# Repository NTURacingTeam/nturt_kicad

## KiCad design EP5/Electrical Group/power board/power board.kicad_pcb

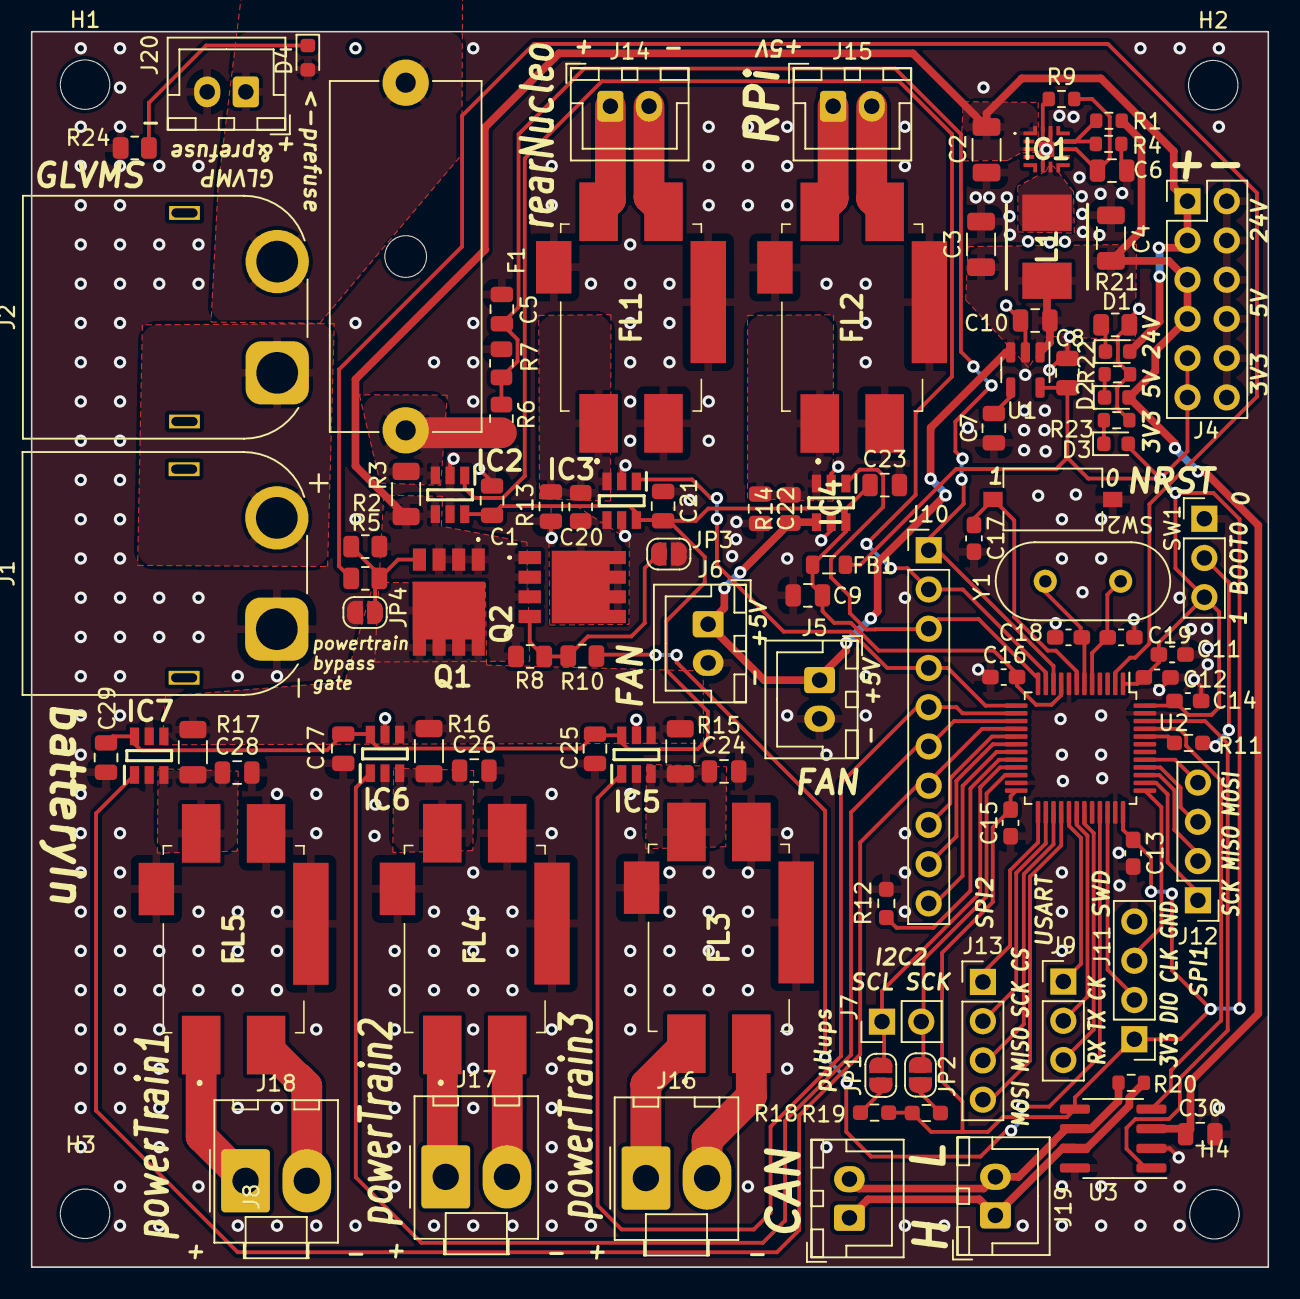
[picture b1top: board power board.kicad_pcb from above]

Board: 2 copper layers, 80.0 x 80.0 mm, 108 parts (0 on the bottom side), 76 nets.

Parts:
C1, C21, C25: 0u1 10V; C_0805_2012Metric
C2: 10u 35V; C_1206_3216Metric
C3, C4: 22u 16V; C_1206_3216Metric
C5: 1u 10V; C_0805_2012Metric
C6: 1u 16V; C_0805_2012Metric
C7: 10nF; C_0805_2012Metric
C8, C9: 10u 5V; C_0805_2012Metric
C10: 4u7 10V; C_0805_2012Metric
C11, C16: 10u; C_0603_1608Metric_Pad1.08x0.95mm_HandSolder
C12, C13, C14, C15, C17: 100n; C_0603_1608Metric_Pad1.08x0.95mm_HandSolder
C18, C19: 30p; C_0603_1608Metric_Pad1.08x0.95mm_HandSolder
C20, C22, C24, C26, C28: 10n; C_0805_2012Metric
C23, C27, C29: 0u1; C_0805_2012Metric
C30: 0u1 16V; C_0805_2012Metric
D1, D4: 24VGood; LED_0603_1608Metric
D2: 5VGood; LED_0603_1608Metric
D3: 3V3Good; LED_0603_1608Metric
F1: Fuse; Fuseholder_Cylinder-5x20mm_Schurter_0031_8201_Horizontal_Op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
FB1: FerriteBead; L_0805_2012Metric
FL1, FL2, FL3, FL4, FL5: BNX026H01L; BNX024H01K
H1, H2, H3, H4: MountingHole; MountingHole_3.2mm_M3
IC1: LMQ66420MC5RXBRQ1; LMR66430R5RXBR
IC2, IC3, IC4, IC5, IC6, IC7: MCP6C04T-100E_CHY; SOT95P280X145-6N
J1: LVBattery; AMASS_XT60PW-M_1x02_P7.20mm_Horizontal
J2: GLVMS; AMASS_XT60PW-M_1x02_P7.20mm_Horizontal
J4: power; PinHeader_2x06_P2.54mm_Vertical
J5: fan1; JST_XH_B2B-XH-A_1x02_P2.50mm_Vertical
J6: fan2; JST_XH_B2B-XH-A_1x02_P2.50mm_Vertical
J7: I2C; PinHeader_1x02_P2.54mm_Vertical
J8, J19: CAN; JST_XH_B2B-XH-A_1x02_P2.50mm_Vertical
J9: UART; PinHeader_1x03_P2.54mm_Vertical
J10: analog; PinHeader_1x10_P2.54mm_Vertical
J11: Serial; PinHeader_1x04_P2.54mm_Vertical
J12: SPI1; PinHeader_1x04_P2.54mm_Vertical
J13: SPI2; PinHeader_1x04_P2.54mm_Vertical
J14: rearBoxNucleo; JST_XH_B2B-XH-A_1x02_P2.50mm_Vertical
J15: Rpi; JST_XH_B2B-XH-A_1x02_P2.50mm_Vertical
J16: powertrain1; Molex_KK-396_A-41791-0002_1x02_P3.96mm_Vertical
J17: powertrain2; Molex_KK-396_A-41791-0002_1x02_P3.96mm_Vertical
J18: powertrain3; Molex_KK-396_A-41791-0002_1x02_P3.96mm_Vertical
J20: GPVMP; JST_XH_B2B-XH-A_1x02_P2.50mm_Vertical
JP1, JP2: I2Cpullup; SolderJumper-2_P1.3mm_Open_RoundedPad1.0x1.5mm
JP3, JP4: byPassGate2; SolderJumper-2_P1.3mm_Open_RoundedPad1.0x1.5mm
L1: 4u7 3A; INDPM5552X300N
Q1, Q2: TPCA8120,L1Q; TPH4R003NLL1Q
R1: 49k9; R_0603_1608Metric
R2, R5, R8, R10: 10k; R_0805_2012Metric
R3, R15, R16, R17: 3m; R_1206_3216Metric
R4: 12k4; R_0603_1608Metric
R6: 47k5; R_0805_2012Metric
R7: 5k9; R_0805_2012Metric
R9: 10k; R_0603_1608Metric
R11, R12: 10k; R_0603_1608Metric_Pad0.98x0.95mm_HandSolder
R13, R14: 10m; R_0805_2012Metric
R18, R19: 3k3; R_0603_1608Metric_Pad0.98x0.95mm_HandSolder
R20: 120R; R_0603_1608Metric
R21, R24: 2k2; R_0805_2012Metric
R22: 220R; R_0603_1608Metric
R23: 150R; R_0603_1608Metric
SW1: BOOT0; PinHeader_1x03_P2.54mm_Vertical
SW2: RESET; SW_Tactile_SPST_NO_Straight_CK_PTS636Sx25SMTRLFS
U1: LP2985-3.3; SOT-23-5
U2: STM32F103C8Tx; LQFP-48_7x7mm_P0.5mm
U3: TJA1051T-3; SOIC-8_3.9x4.9mm_P1.27mm
Y1: 8MHz; Crystal_HC49-U_Vertical

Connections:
5V_BOOT: IC1.8 (BOOT_1), IC1.18 (NC_7)
5V_PGood: IC1.14 (PG), R9.1
+5V: C3.1, C4.1, C10.1, C30.1, D2.2 (A), IC4.4 (VIM), J4.5, J4.7, J5.1, J6.1, L1.1, R1.1, R14.1, U1.1 (VIN), U1.3 (ON/~OFF), U3.3 (VCC)
+24V: C2.1, D1.2 (A), IC1.1 (EN_1), IC1.3 (VIN), IC1.16 (NC_6), IC2.4 (VIM), J4.1, J4.3, Q1.1 (S_1), Q1.2 (S_2), Q1.3 (S_3), Q2.1 (S_1), Q2.2 (S_2), Q2.3 (S_3), R2.1, R3.1, R8.1
/+24V_BAT: J1.2, J2.1
/+24V_prefuse: D4.2 (A), F1.1, J2.2, J20.1
/+24V_premessure: F1.2, IC2.3 (VIP), R3.2, R6.1
/BOOT0: R11.2, U2.44 (BOOT0)
/BOOT1: R12.2, U2.20 (PB2)
/CAN_RX: U2.45 (PB8), U3.4 (RXD)
/CAN_TX: U2.46 (PB9), U3.1 (TXD)
/I2C2_SCK: J7.2, JP2.2 (B), U2.22 (PB11)
/I2C2_SCL: J7.1, JP1.2 (B), U2.21 (PB10)
/I_LVrear: IC3.1 (VOUT), J10.4, U2.13 (PA3)
/I_Rpi: IC4.1 (VOUT), J10.3, U2.12 (PA2)
/I_all: IC2.1 (VOUT), J10.2, U2.11 (PA1)
/I_powerTrain1: IC5.1 (VOUT), J10.5, U2.14 (PA4)
/I_powerTrain2: IC6.1 (VOUT), J10.6, U2.15 (PA5)
/I_powerTrain3: IC7.1 (VOUT), J10.7, U2.16 (PA6)
/NRST: C17.1, SW2.2, U2.7 (NRST)
/OSC1: C19.1, U2.5 (PD0), Y1.1
/OSC2: C18.1, U2.6 (PD1), Y1.2
/SPI1_CS: J12.1, U2.38 (PA15)
/SPI1_MISO: J12.3, U2.40 (PB4)
/SPI1_MOSI: J12.4, U2.41 (PB5)
/SPI1_SCK: J12.2, U2.39 (PB3)
/SPI2_CS: J13.1, U2.25 (PB12)
/SPI2_MISO: J13.3, U2.27 (PB14)
/SPI2_MOSI: J13.4, U2.28 (PB15)
/SPI2_SCK: J13.2, U2.26 (PB13)
/SWCLK: J11.3, U2.37 (PA14)
/SWDIO: J11.2, U2.34 (PA13)
/USART_CK: J9.1, U2.29 (PA8)
/USART_RX: J9.3, U2.31 (PA10)
/USART_TX: J9.2, U2.30 (PA9)
/V_all: C5.1, J10.1, R6.2, R7.1, U2.10 (PA0)
/emptyAnalog1: J10.8, U2.17 (PA7)
/emptyAnalog2: J10.9, U2.18 (PB0)
/emptyAnalog3: J10.10, U2.19 (PB1)
/inbox/5V_RPi: C22.1, FL2.1 (BIAS), IC4.3 (VIP), R14.2
/inbox/24V_rearNucleo: C20.1, FL1.1 (BIAS), IC3.3 (VIP), R13.2
/main24vGate1: R5.1, U2.2 (PC13)
/main24vGate2: R10.1, U2.33 (PA12)
/outbox/24V_powertrain1: C24.1, FL3.2 (CIRCUIT+BIAS), IC5.3 (VIP), R15.2
/outbox/24V_powertrain2: C26.1, FL4.2 (CIRCUIT+BIAS), IC6.3 (VIP), R16.2
/outbox/24V_powertrain3: C28.1, FL5.2 (CIRCUIT+BIAS), IC7.3 (VIP), R17.2
/power/5V_SW: IC1.7 (SW), L1.2
/power/5Vraw: IC1.11 (VOUT/FB), R1.2, R4.1
CANH: J8.1, J19.1, R20.2, U3.7 (CANH)
CANL: J8.2, J19.2, R20.1, U3.6 (CANL)
GND: C1.2, C2.2, C3.2, C4.2, C5.2, C6.2, C7.2, C8.2, C9.2, C10.2, C11.2, C12.2, C13.2, C14.2, C15.2, C16.2, C17.2, C18.2, C19.2, C20.2, C21.2, C22.2, C23.2, C24.2, C25.2, C26.2, C27.2, C28.2, C29.2, C30.2, FL1.3 (POWER_SUPPLY_GND), FL1.B4 (CIRCUIT_GROUND_2), FL1.C4 (CIRCUIT_GROUND_3), FL2.3 (POWER_SUPPLY_GND), FL2.B4 (CIRCUIT_GROUND_2), FL2.C4 (CIRCUIT_GROUND_3), FL3.A4 (CIRCUIT_GROUND_1), FL3.B4 (CIRCUIT_GROUND_2), FL3.C4 (CIRCUIT_GROUND_3), FL4.A4 (CIRCUIT_GROUND_1), FL4.B4 (CIRCUIT_GROUND_2), FL4.C4 (CIRCUIT_GROUND_3), FL5.A4 (CIRCUIT_GROUND_1), FL5.B4 (CIRCUIT_GROUND_2), FL5.C4 (CIRCUIT_GROUND_3), IC1.6 (PGND), IC1.13 (MODE/SYNC), IC1.15 (GND/DAP), IC2.2 (VSS), IC2.5 (VREF), IC3.2 (VSS), IC3.5 (VREF), IC4.2 (VSS), IC4.5 (VREF), IC5.2 (VSS), IC5.5 (VREF), IC6.2 (VSS), IC6.5 (VREF), IC7.2 (VSS), IC7.5 (VREF), J1.1, J4.2, J4.4, J4.6, J4.8, J4.10, J4.12, J5.2, J6.2, J11.4, J20.2, JP3.1 (A), JP4.1 (A), R4.2, R7.2, R12.1, R21.2, R22.2, R23.2, R24.2, SW1.1 (A), SW2.1, U1.2 (GND), U2.8 (VSSA), U2.23 (VSS), U2.35 (VSS), U2.47 (VSS), U3.2 (GND), U3.8 (S)
unnamed: D1.1 (K), R21.1
unnamed: D2.1 (K), R22.1
unnamed: D3.1 (K), R23.1
unnamed: D4.1 (K), R24.1
unnamed: FL1.2 (CIRCUIT+BIAS), J14.1
unnamed: FL1.A4 (CIRCUIT_GROUND_1), J14.2
unnamed: FL2.2 (CIRCUIT+BIAS), J15.1
unnamed: FL2.A4 (CIRCUIT_GROUND_1), J15.2
unnamed: FL3.1 (BIAS), J16.1
unnamed: FL3.3 (POWER_SUPPLY_GND), J16.2
unnamed: FL4.1 (BIAS), J17.1
unnamed: FL4.3 (POWER_SUPPLY_GND), J17.2
unnamed: FL5.1 (BIAS), J18.1
unnamed: FL5.3 (POWER_SUPPLY_GND), J18.2
unnamed: C6.1, IC1.10 (VCC), R9.2
unnamed: JP1.1 (A), R18.2
unnamed: JP2.1 (A), R19.2
unnamed: JP3.2 (B), Q2.4 (G), R8.2, R10.2
unnamed: JP4.2 (B), Q1.4 (G), R2.2, R5.2
unnamed: R11.1, SW1.2 (B)
unnamed: C7.1, U1.4 (BP)
VD: IC5.4 (VIM), IC6.4 (VIM), IC7.4 (VIM), Q1.5 (D_1), Q1.6 (D_2), Q1.7 (D_3), Q1.8 (D_4), Q1.9 (D_5), R15.1, R16.1, R17.1
VDC: IC3.4 (VIM), Q2.5 (D_1), Q2.6 (D_2), Q2.7 (D_3), Q2.8 (D_4), Q2.9 (D_5), R13.1
VDD: C8.1, C11.1, C12.1, C13.1, C14.1, C15.1, D3.2 (A), FB1.1, J4.9, J4.11, J11.1, R18.1, R19.1, SW1.3 (C), U1.5 (VOUT), U2.1 (VBAT), U2.24 (VDD), U2.36 (VDD), U2.48 (VDD), U3.5 (VIO)
VDDA: C1.1, C9.1, C16.1, C21.1, C23.1, C25.1, C27.1, C29.1, FB1.2, IC2.6 (VDD), IC3.6 (VDD), IC4.6 (VDD), IC5.6 (VDD), IC6.6 (VDD), IC7.6 (VDD), U2.9 (VDDA)

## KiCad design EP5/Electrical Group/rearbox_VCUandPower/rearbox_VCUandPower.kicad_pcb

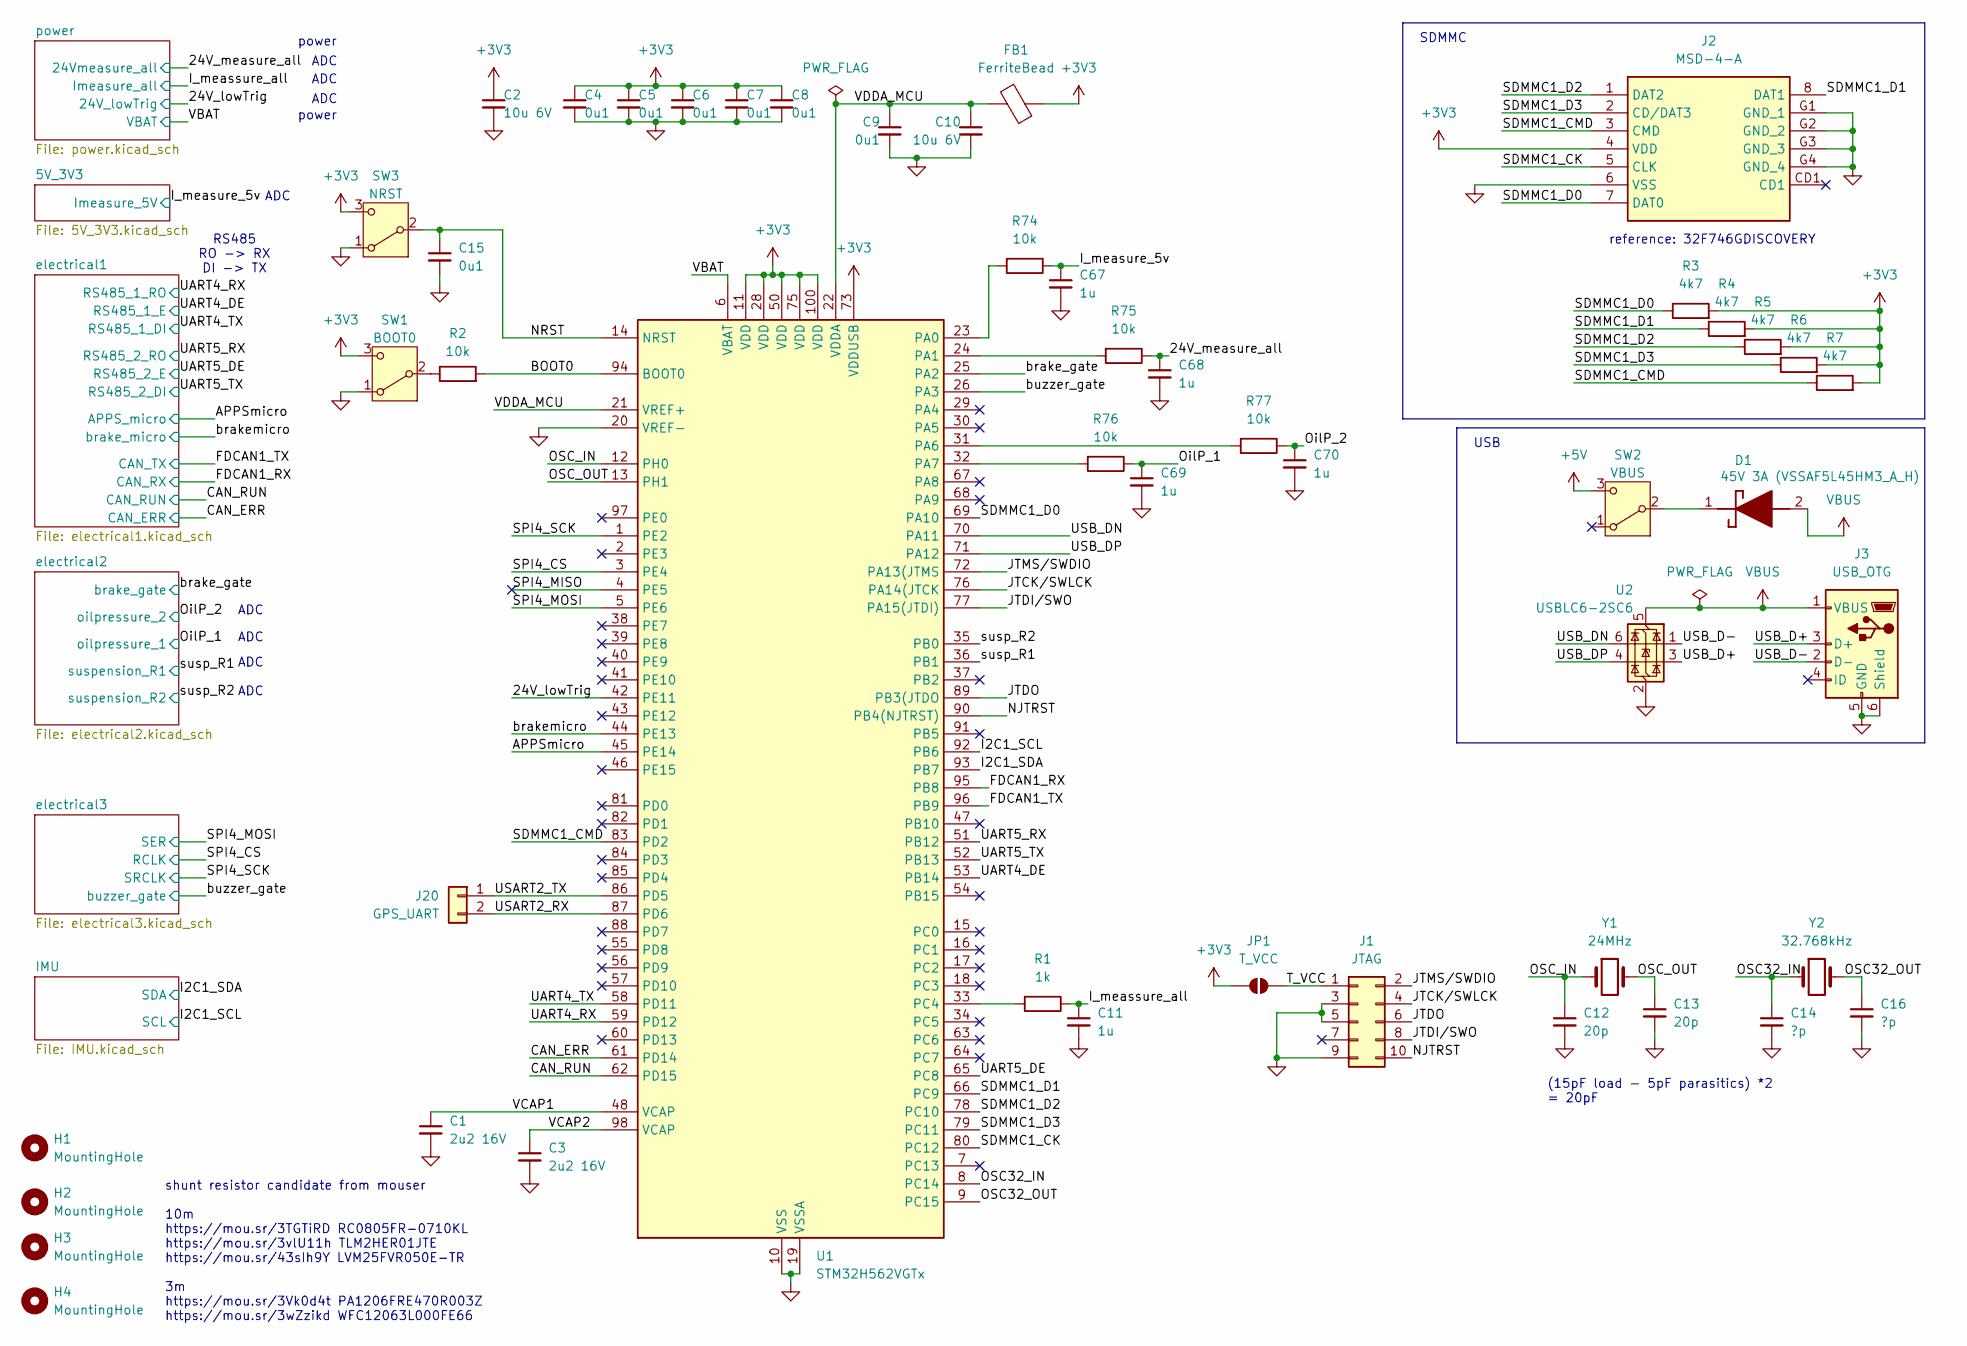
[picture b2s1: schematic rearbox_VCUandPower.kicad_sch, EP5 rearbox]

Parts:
C1, C3: 2u2 16V; C_0603_1608Metric
C2, C10: 10u 6V; C_0603_1608Metric
C4, C5, C6, C7, C8, C9, C15: 0u1; C_0603_1608Metric
C11, C67, C68, C69, C70: 1u; C_0603_1608Metric
C12, C13: 20p; C_0603_1608Metric
C14, C16: ?p; C_0603_1608Metric
D1: 45V 3A (VSSAF5L45HM3_A_H); SODFL5226X100N; Mouser Part Number 78-VSSAF5L45HM3_A/H
FB1: FerriteBead; L_0805_2012Metric
H1, H2, H3, H4: MountingHole; MountingHole_3.2mm_M3
J1: JTAG; IDC-Header_2x05_P2.00mm_Vertical
J2: MSD-4-A; MSD4A; Mouser Part Number 179-MSD-4-A
J3: USB_OTG; USB_Micro-B_Wuerth_629105150521
J20: GPS_UART; JST_XH_B2B-XH-A_1x02_P2.50mm_Vertical
JP1: T_VCC; SolderJumper-2_P1.3mm_Open_RoundedPad1.0x1.5mm
R1: 1k; R_0603_1608Metric
R2, R74, R75, R76, R77: 10k; R_0603_1608Metric
R3, R4, R5, R6, R7: 4k7; R_0603_1608Metric
SW1: BOOT0; PinHeader_1x03_P2.54mm_Vertical
SW2: VBUS; PinHeader_1x03_P2.54mm_Vertical
SW3: NRST; PinHeader_1x03_P2.54mm_Vertical
U1: STM32H562VGTx; LQFP-100_14x14mm_P0.5mm
U2: USBLC6-2SC6; SOT-23-6
Y1: 24MHz; Crystal_C38-LF_D3.0mm_L8.0mm_Vertical
Y2: 32.768kHz; Crystal_C38-LF_D3.0mm_L8.0mm_Vertical

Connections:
+3V3: C2.1, C4.1, C5.1, C6.1, C7.1, C8.1, FB1.1, J2.4 (VDD), JP1.1 (A), R3.2, R4.2, R5.2, R6.2, R7.2, SW1.3 (C), SW3.3 (C), U1.11 (VDD), U1.28 (VDD), U1.50 (VDD), U1.73 (VDDUSB), U1.75 (VDD), U1.100 (VDD); also elsewhere on the board
+5V: SW2.3 (C); also elsewhere on the board
/24V_lowTrig: U1.42 (PE11); also elsewhere on the board
/24V_measure_all: C68.1, R75.1; also elsewhere on the board
/APPSmicro: U1.45 (PE14); also elsewhere on the board
/BOOT0: R2.2, U1.94 (BOOT0)
/CAN_ERR: U1.61 (PD14); also elsewhere on the board
/CAN_RUN: U1.62 (PD15); also elsewhere on the board
/FDCAN1_RX: U1.95 (PB8); also elsewhere on the board
/FDCAN1_TX: U1.96 (PB9); also elsewhere on the board
/I2C1_SCL: U1.92 (PB6); also elsewhere on the board
/I2C1_SDA: U1.93 (PB7); also elsewhere on the board
/I_meassure_all: C11.1, R1.1; also elsewhere on the board
/I_measure_5v: C67.1, R74.1; also elsewhere on the board
/JTCK/SWLCK: J1.4, U1.76 (PA14(JTCK)
/JTDI/SWO: J1.8, U1.77 (PA15(JTDI))
/JTDO: J1.6, U1.89 (PB3(JTDO)
/JTMS/SWDIO: J1.2, U1.72 (PA13(JTMS)
/NJTRST: J1.10, U1.90 (PB4(NJTRST))
/NRST: C15.1, SW3.2 (B), U1.14 (NRST)
/OSC32_IN: C14.1, U1.8 (PC14), Y2.1
/OSC32_OUT: C16.1, U1.9 (PC15), Y2.2
/OSC_IN: C12.1, U1.12 (PH0), Y1.1
/OSC_OUT: C13.1, U1.13 (PH1), Y1.2
/SDMMC1_CK: J2.5 (CLK), U1.80 (PC12)
/SDMMC1_CMD: J2.3 (CMD), R7.1, U1.83 (PD2)
/SDMMC1_D0: J2.7 (DAT0), R3.1, U1.69 (PA10)
/SDMMC1_D1: J2.8 (DAT1), R4.1, U1.66 (PC9)
/SDMMC1_D2: J2.1 (DAT2), R5.1, U1.78 (PC10)
/SDMMC1_D3: J2.2 (CD/DAT3), R6.1, U1.79 (PC11)
/SPI4_CS: U1.3 (PE4); also elsewhere on the board
/SPI4_MISO: U1.4 (PE5)
/SPI4_MOSI: U1.5 (PE6); also elsewhere on the board
/SPI4_SCK: U1.1 (PE2); also elsewhere on the board
/T_VCC: J1.1, JP1.2 (B)
/UART4_DE: U1.53 (PB14); also elsewhere on the board
/UART4_RX: U1.59 (PD12); also elsewhere on the board
/UART4_TX: U1.58 (PD11); also elsewhere on the board
/UART5_DE: U1.65 (PC8); also elsewhere on the board
/UART5_RX: U1.51 (PB12); also elsewhere on the board
/UART5_TX: U1.52 (PB13); also elsewhere on the board
/USART2_RX: J20.2, U1.87 (PD6)
/USART2_TX: J20.1, U1.86 (PD5)
/USB_D+: J3.3 (D+), U2.3 (I/O2)
/USB_D-: J3.2 (D-), U2.1 (I/O1)
/USB_DN: U1.70 (PA11), U2.6 (I/O1)
/USB_DP: U1.71 (PA12), U2.4 (I/O2)
/VBAT: U1.6 (VBAT); also elsewhere on the board
/VCAP1: C1.1, U1.48 (VCAP)
/VCAP2: C3.1, U1.98 (VCAP)
/VDDA_MCU: C9.1, C10.1, FB1.2, U1.21 (VREF+), U1.22 (VDDA)
/brake_gate: U1.25 (PA2); also elsewhere on the board
/brakemicro: U1.44 (PE13); also elsewhere on the board
/buzzer_gate: U1.26 (PA3); also elsewhere on the board
GND: C1.2, C2.2, C3.2, C4.2, C5.2, C6.2, C7.2, C8.2, C9.2, C10.2, C11.2, C12.2, C13.2, C14.2, C15.2, C16.2, C67.2, C68.2, C69.2, C70.2, J1.3, J1.5, J1.9, J2.6 (VSS), J2.G1 (GND_1), J2.G2 (GND_2), J2.G3 (GND_3), J2.G4 (GND_4), J3.5 (GND), J3.6 (Shield), SW1.1 (A), SW3.1 (A), U1.10 (VSS), U1.19 (VSSA), U1.20 (VREF-), U1.27 (VSS), U1.49 (VSS), U1.74 (VSS), U1.99 (VSS), U2.2 (GND); also elsewhere on the board
unnamed: D1.1 (K), SW2.2 (B)
unnamed: R2.1, SW1.2 (B)
unnamed: R74.2, U1.23 (PA0)
unnamed: R75.2, U1.24 (PA1)
unnamed: R77.2, U1.31 (PA6)
unnamed: R76.2, U1.32 (PA7)
unnamed: R1.2, U1.33 (PC4)
VBUS: D1.2 (A), J3.1 (VBUS), U2.5 (VBUS)
oilpressure_shunt_1: C69.1, R76.1; also elsewhere on the board
oilpressure_shunt_2: C70.1, R77.1; also elsewhere on the board
suspension_R1: U1.36 (PB1); also elsewhere on the board
suspension_R2: U1.35 (PB0); also elsewhere on the board

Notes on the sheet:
ADC
USB
power
SDMMC
reference: 32F746GDISCOVERY
(15pF load - 5pF parasitics) *2 = 20pF
shunt resistor candidate from mouser 10m https://mou.sr/3TGTiRD RC0805FR-0710KL https://mou.sr/3vlU11h TLM2HER01JTE https://mou.sr/43sIh9Y LVM25FVR050E-TR 3m https://mou.sr/3Vk0d4t PA1206FRE470R003Z https://mou.sr/3wZzikd WFC12063L000FE66
RS485 RO -> RX DI -> TX

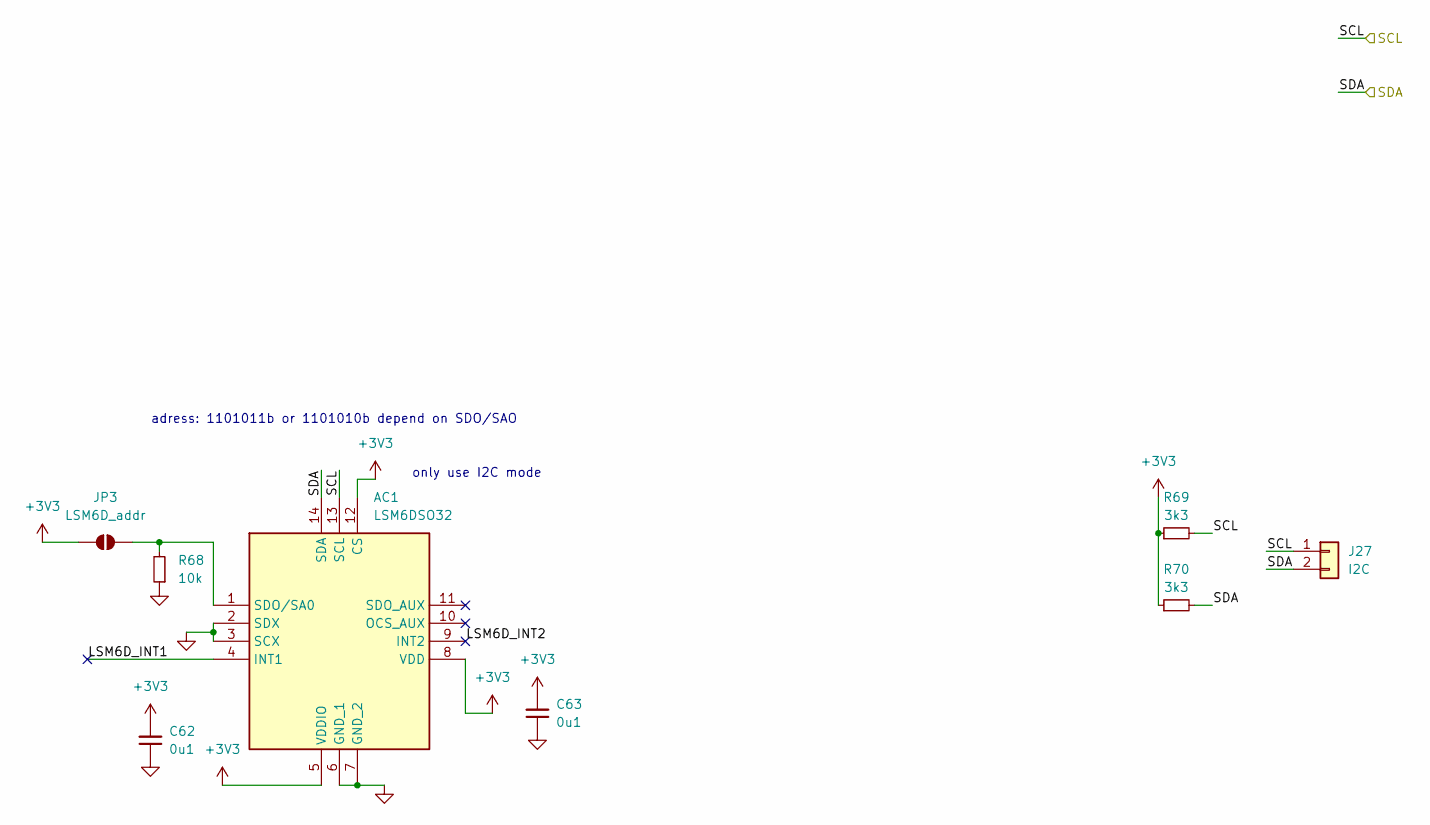
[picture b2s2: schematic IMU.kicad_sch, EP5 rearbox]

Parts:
AC1: LSM6DSO32; LGA-14_1; Mouser Part Number 511-LSM6DSOXTR
C62, C63: 0u1; C_0603_1608Metric
J27: I2C; JST_XH_B2B-XH-A_1x02_P2.50mm_Vertical
JP3: LSM6D_addr; SolderJumper-2_P1.3mm_Open_RoundedPad1.0x1.5mm
R68: 10k; R_0603_1608Metric
R69, R70: 3k3; R_0603_1608Metric

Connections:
+3V3: AC1.5 (VDDIO), AC1.8 (VDD), AC1.12 (CS), C62.2, C63.2, JP3.1 (A), R69.1, R70.1; also elsewhere on the board
/I2C1_SCL: AC1.13 (SCL), J27.1, R69.2; also elsewhere on the board
/I2C1_SDA: AC1.14 (SDA), J27.2, R70.2; also elsewhere on the board
/IMU/LSM6D_INT1: AC1.4 (INT1)
/IMU/LSM6D_INT2: AC1.9 (INT2)
GND: AC1.2 (SDX), AC1.3 (SCX), AC1.6 (GND_1), AC1.7 (GND_2), C62.1, C63.1, R68.1; also elsewhere on the board
unnamed: AC1.1 (SDO/SA0), JP3.2 (B), R68.2

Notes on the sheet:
adress: 1101011b or 1101010b depend on SDO/SAO
only use I2C mode

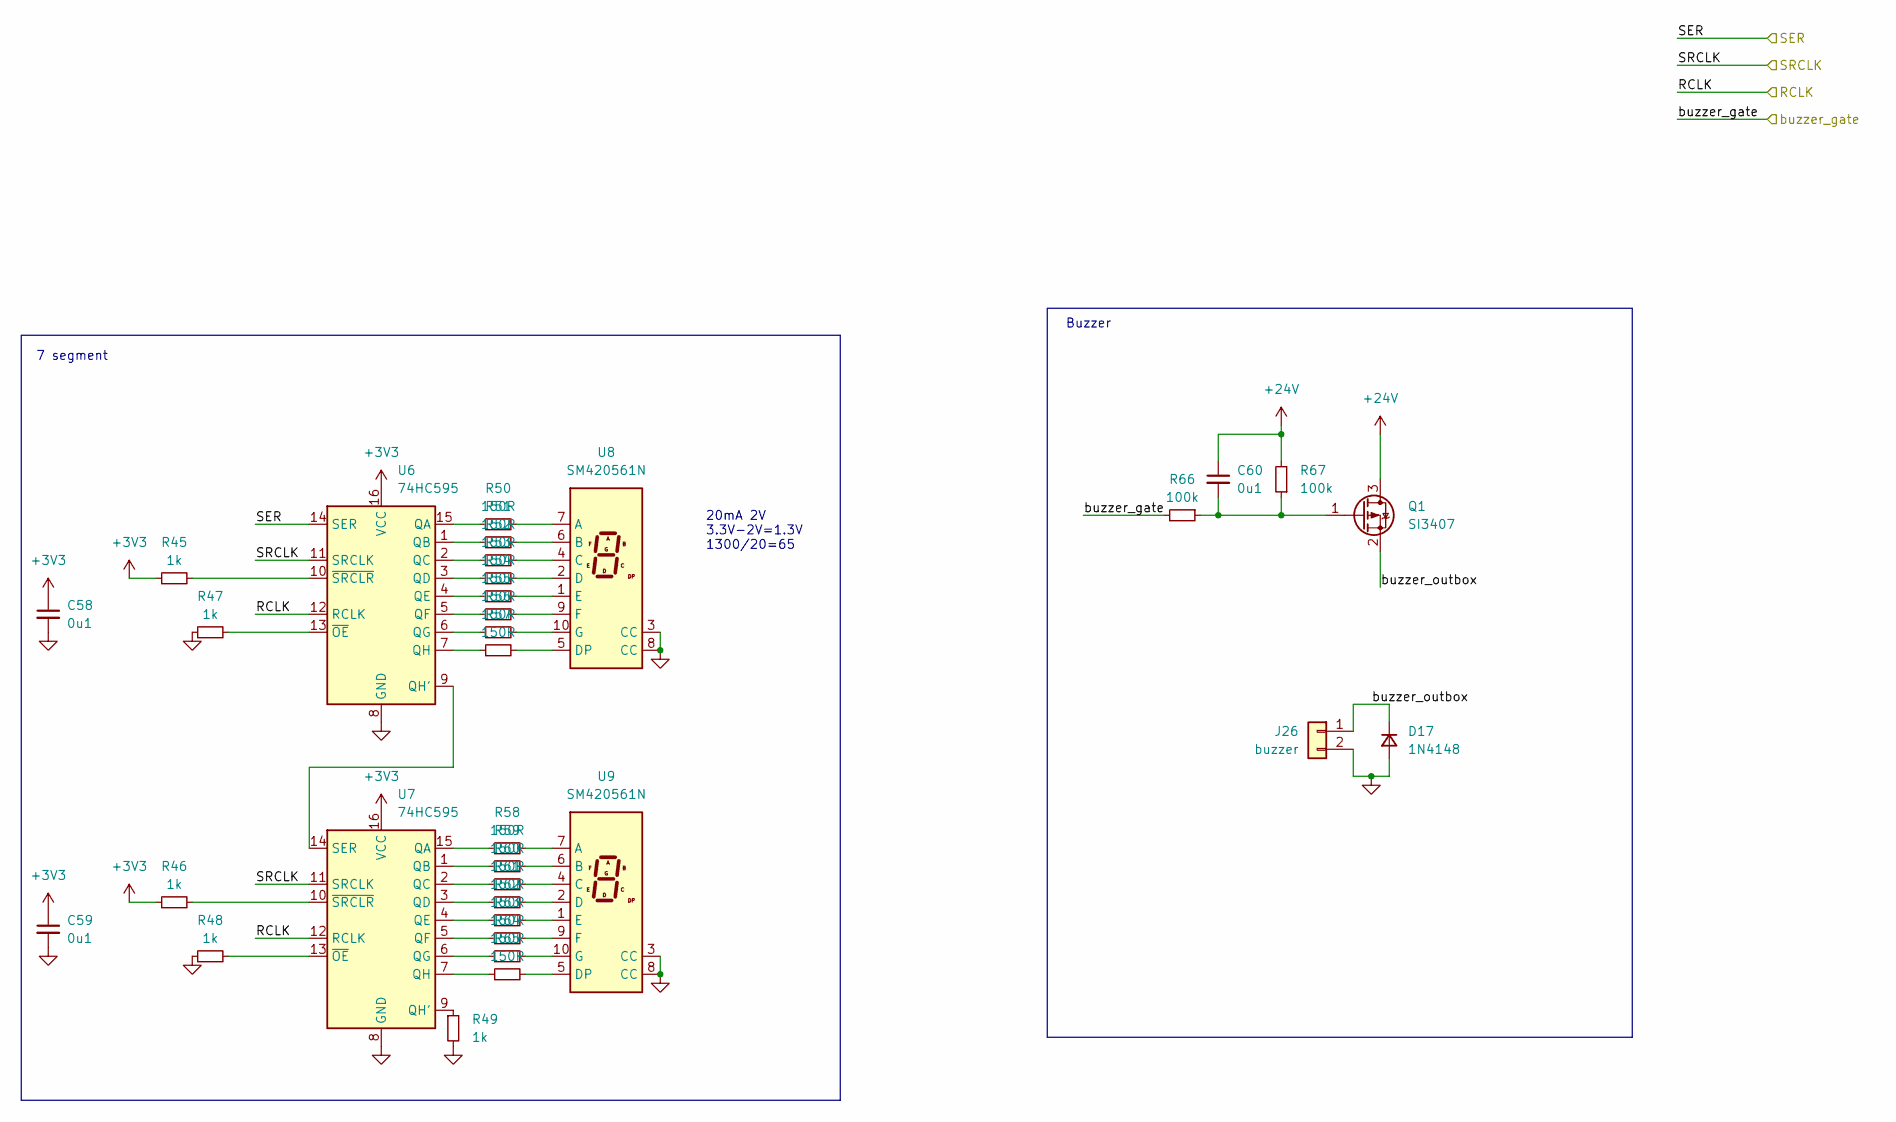
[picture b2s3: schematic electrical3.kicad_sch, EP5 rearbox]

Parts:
C58, C59, C60: 0u1; C_0603_1608Metric
D17: 1N4148; D_MiniMELF
J26: buzzer; JST_XH_B2B-XH-A_1x02_P2.50mm_Vertical
Q1: SI3407; SOT-23-3
R45, R46, R47, R48, R49: 1k; R_0603_1608Metric
R50, R51, R52, R53, R54, R55, R56, R57, R58, R59, R60, R61, R62, R63, R64, R65: 150R; R_0603_1608Metric
R66, R67: 100k; R_0603_1608Metric
U6, U7: 74HC595; SOIC-16_3.9x9.9mm_P1.27mm
U8, U9: SM420561N; 7SegmentLED_LTS6760_LTS6780

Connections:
+3V3: C58.1, C59.1, R45.1, R46.1, U6.16 (VCC), U7.16 (VCC); also elsewhere on the board
+24V: C60.1, Q1.3 (D), R67.2; also elsewhere on the board
/SPI4_CS: U6.12 (RCLK), U7.12 (RCLK); also elsewhere on the board
/SPI4_MOSI: U6.14 (SER); also elsewhere on the board
/SPI4_SCK: U6.11 (SRCLK), U7.11 (SRCLK); also elsewhere on the board
/buzzer_gate: R66.2; also elsewhere on the board
/electrical3/buzzer_outbox: D17.1 (K), J26.1, Q1.2 (S)
GND: C58.2, C59.2, D17.2 (A), J26.2, R47.1, R48.1, R49.2, U6.8 (GND), U7.8 (GND), U8.3 (CC), U8.8 (CC), U9.3 (CC), U9.8 (CC); also elsewhere on the board
unnamed: C60.2, Q1.1 (G), R66.1, R67.1
unnamed: R50.1, U6.15 (QA)
unnamed: R51.1, U6.1 (QB)
unnamed: R52.1, U6.2 (QC)
unnamed: R53.1, U6.3 (QD)
unnamed: R54.1, U6.4 (QE)
unnamed: R55.1, U6.5 (QF)
unnamed: R56.1, U6.6 (QG)
unnamed: U6.9 (QH'), U7.14 (SER)
unnamed: R57.1, U6.7 (QH)
unnamed: R47.2, U6.13 (~OE)
unnamed: R45.2, U6.10 (~SRCLR)
unnamed: R58.1, U7.15 (QA)
unnamed: R59.1, U7.1 (QB)
unnamed: R60.1, U7.2 (QC)
unnamed: R61.1, U7.3 (QD)
unnamed: R62.1, U7.4 (QE)
unnamed: R63.1, U7.5 (QF)
unnamed: R64.1, U7.6 (QG)
unnamed: R49.1, U7.9 (QH')
unnamed: R65.1, U7.7 (QH)
unnamed: R48.2, U7.13 (~OE)
unnamed: R46.2, U7.10 (~SRCLR)
unnamed: R50.2, U8.7 (A)
unnamed: R51.2, U8.6 (B)
unnamed: R52.2, U8.4 (C)
unnamed: R53.2, U8.2 (D)
unnamed: R57.2, U8.5 (DP)
unnamed: R54.2, U8.1 (E)
unnamed: R55.2, U8.9 (F)
unnamed: R56.2, U8.10 (G)
unnamed: R58.2, U9.7 (A)
unnamed: R59.2, U9.6 (B)
unnamed: R60.2, U9.4 (C)
unnamed: R61.2, U9.2 (D)
unnamed: R65.2, U9.5 (DP)
unnamed: R62.2, U9.1 (E)
unnamed: R63.2, U9.9 (F)
unnamed: R64.2, U9.10 (G)

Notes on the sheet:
Buzzer
7 segment
20mA 2V 3.3V-2V=1.3V 1300/20=65

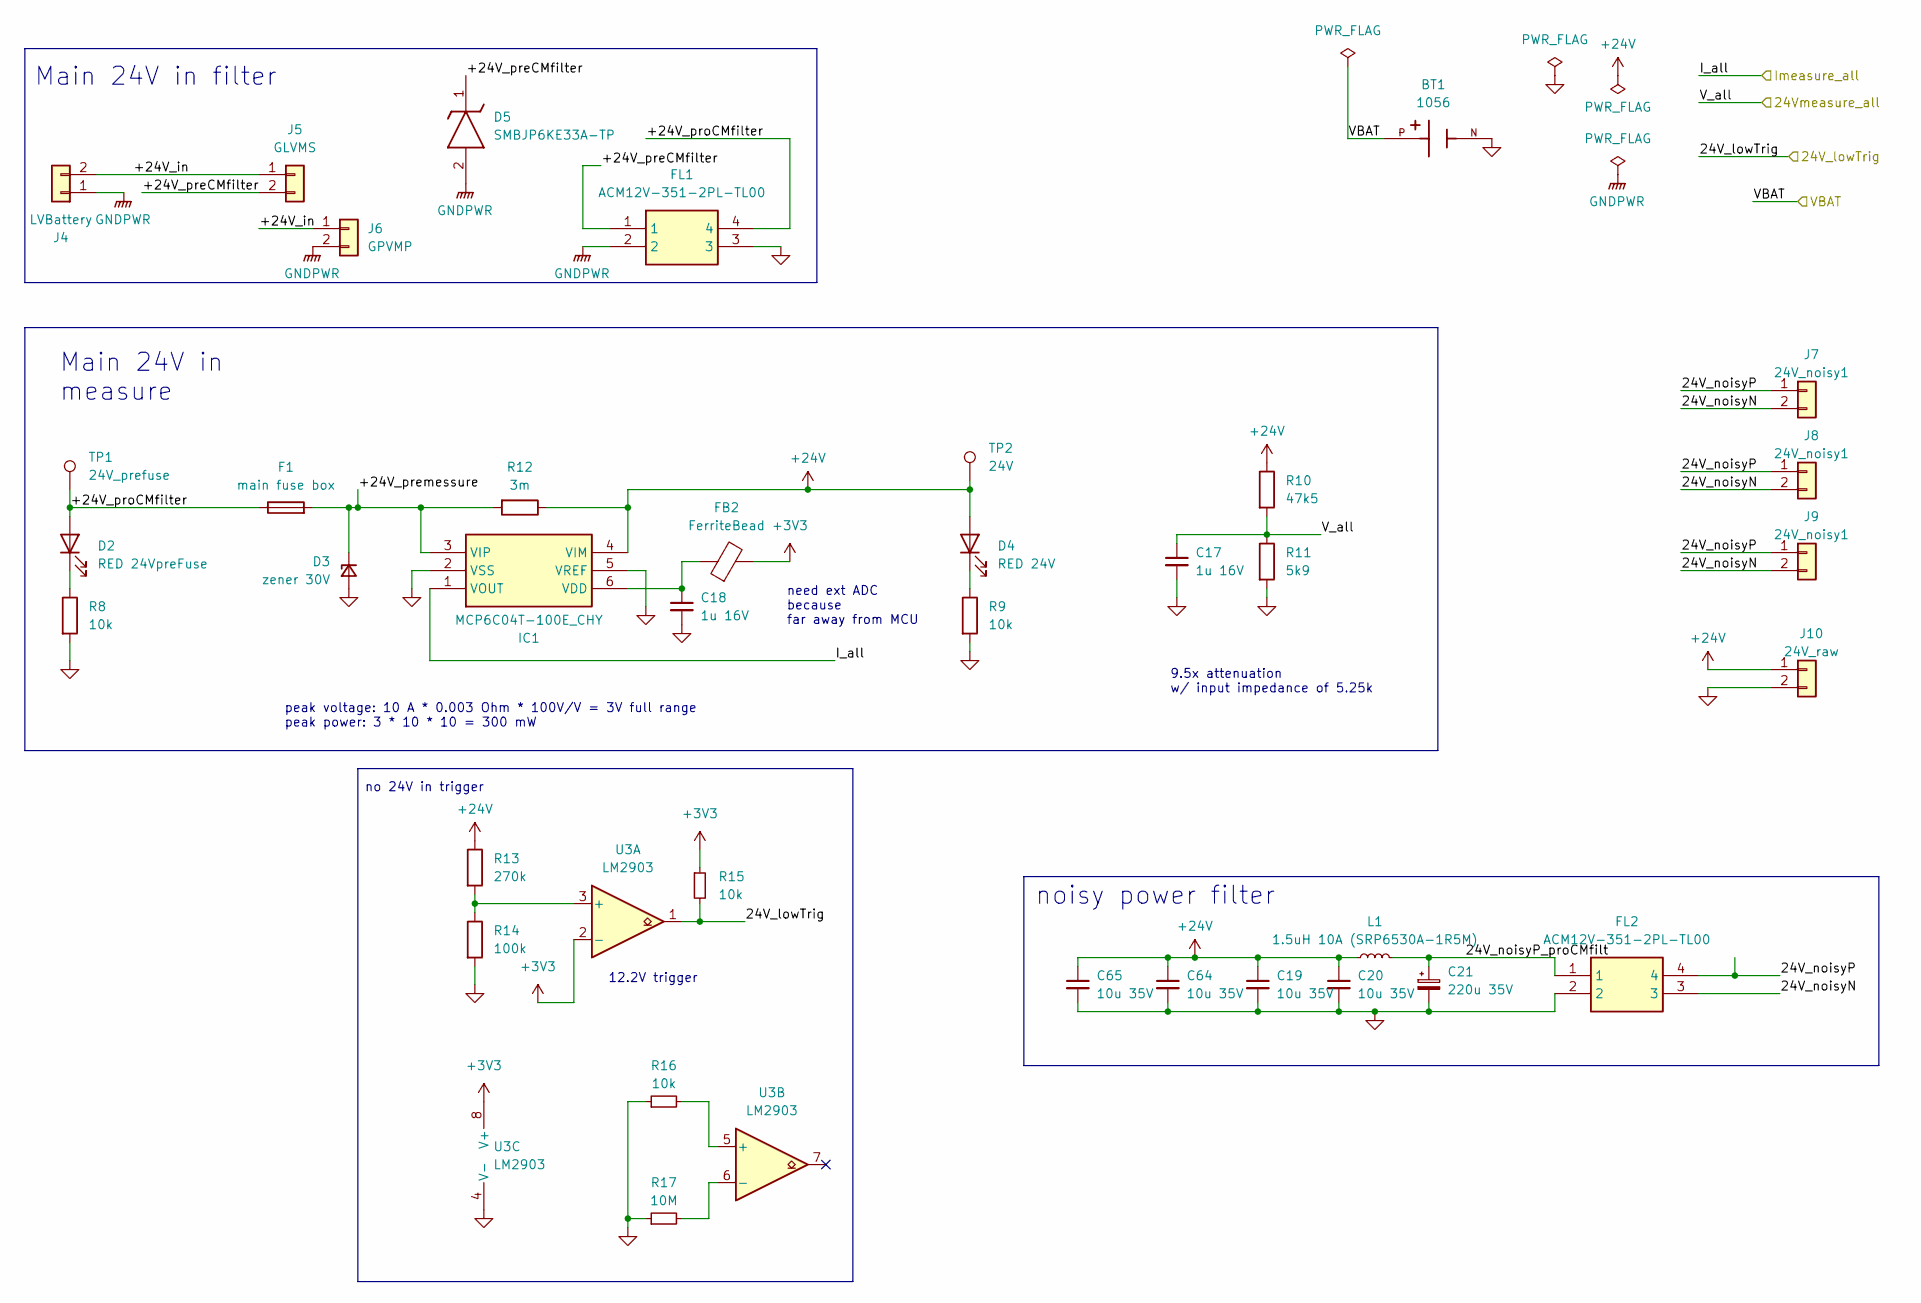
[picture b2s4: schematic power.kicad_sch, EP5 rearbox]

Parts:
BT1: 1056; BAT_1056; PARTREV D
C17, C18: 1u 16V; C_0603_1608Metric
C19, C20, C64, C65: 10u 35V; C_1206_3216Metric
C21: 220u 35V; CP_Radial_D8.0mm_P3.80mm
D2: RED 24VpreFuse; LED_0603_1608Metric
D3: zener 30V; D_MiniMELF
D4: RED 24V; LED_0603_1608Metric
D5: SMBJP6KE33A-TP; DIOM5336X262N; Mouser Part Number 833-SMBJP6KE33A-TP
F1: main fuse box; Fuseholder_Cylinder-5x20mm_Schurter_0031_8201_Horizontal_Op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
FB2: FerriteBead; L_0805_2012Metric
FL1, FL2: ACM12V-351-2PL-TL00; ACM12V3512PLTL00; Mouser Part Number 810-ACM12V-351-2PLTL
IC1: MCP6C04T-100E_CHY; SOT95P280X145-6N; Mouser Part Number 579-MCP6C04T100ECHY
J4: LVBattery; AMASS_XT60PW-M_1x02_P7.20mm_Horizontal
J5: GLVMS; JST_VH_B2P-VH_1x02_P3.96mm_Vertical
J6: GPVMP; JST_XH_B2B-XH-A_1x02_P2.50mm_Vertical
J7, J8, J9: 24V_noisy1; Molex_KK-396_A-41791-0002_1x02_P3.96mm_Vertical
J10: 24V_raw; Molex_KK-396_A-41791-0002_1x02_P3.96mm_Vertical
L1: 1.5uH 10A (SRP6530A-1R5M); SRR6040A180M
R8, R9, R15, R16: 10k; R_0603_1608Metric
R10: 47k5; R_0805_2012Metric
R11: 5k9; R_0805_2012Metric
R12: 3m; R_1206_3216Metric
R13: 270k; R_0805_2012Metric
R14: 100k; R_0805_2012Metric
R17: 10M; R_0603_1608Metric
TP1: 24V_prefuse; TestPoint_Pad_D1.0mm
TP2: 24V; TestPoint_Pad_D1.0mm
U3: LM2903; SOIC-8_3.9x4.9mm_P1.27mm

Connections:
+3V3: FB2.2, R15.1, U3.2 (-), U3.8 (V+); also elsewhere on the board
+24V: C19.1, C20.1, C64.1, C65.1, D4.2 (A), IC1.4 (VIM), J10.1, L1.1, R10.1, R12.1, R13.1, TP2.1; also elsewhere on the board
/24V_lowTrig: R15.2, U3.1; also elsewhere on the board
/24V_measure_all: C17.1, R10.2, R11.1; also elsewhere on the board
/I_meassure_all: IC1.1 (VOUT); also elsewhere on the board
/VBAT: BT1.P; also elsewhere on the board
/power/24V_noisyN: FL2.3, J7.2, J8.2, J9.2
/power/24V_noisyP: FL2.4, J7.1, J8.1, J9.1
/power/24V_noisyP_proCMfilt: C21.1, FL2.1, L1.2
/power/+24V_in: J4.2, J5.1, J6.1
/power/+24V_preCMfilter: D5.1 (K), FL1.1, J5.2
/power/+24V_premessure: D3.1 (K), F1.2, IC1.3 (VIP), R12.2
/power/+24V_proCMfilter: D2.2 (A), F1.1, FL1.4, TP1.1
GND: BT1.N, C17.2, C18.2, C19.2, C20.2, C21.2, C64.2, C65.2, D3.2 (A), FL1.3, FL2.2, IC1.2 (VSS), IC1.5 (VREF), J10.2, R8.2, R9.2, R11.2, R14.2, R16.1, R17.1, U3.4 (V-); also elsewhere on the board
GNDPWR: D5.2 (A), FL1.2, J4.1, J6.2
unnamed: D2.1 (K), R8.1
unnamed: D4.1 (K), R9.1
unnamed: C18.1, FB2.1, IC1.6 (VDD)
unnamed: R13.2, R14.1, U3.3 (+)
unnamed: R16.2, U3.5 (+)
unnamed: R17.2, U3.6 (-)

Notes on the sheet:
peak voltage: 10 A * 0.003 Ohm * 100V/V = 3V full range peak power: 3 * 10 * 10 = 300 mW
need ext ADC because far away from MCU
no 24V in trigger
9.5x attenuation w/ input impedance of 5.25k
Main 24V in filter
noisy power filter
Main 24V in measure
12.2V trigger
